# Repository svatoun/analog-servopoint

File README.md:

# analog-servopoint

Analog-servopoint je zařízení určené k ovládání servo a spínaných (zap/vyp) výstupů pro analogově řízený model železnice. Základní deska má tyto vstupy a výstupy:

1. Vstup z maticové klávesnice 4x4 tlačítek. Funguje jak pro spínací mžiková tlačítka, tak pro přepínací tlačítka. U přepínacích tlačítek může mít význam přepnutí do obou poloh.
2. Ovládání až 8 modelářských serv. 
3. 8 tranzistorem spínaných výstupů, zatížení cca 500mA/výstup, celkem 2,5A

Software poskytuje následující funkce:

### Ovládání serva
1. Určení 2 poloh (levá, pravá) pro každé servo.
2. Určení rychlosti přestavování serva.
3. Interaktivní kalibrace serva
4. Plynulé přestavení serva do předdefinované pravé/levé polohy, nebo na libovolný úhel
5. Postupné spínaní serv, eliminaci proudové špičky, omezení zákmitu serva
6. "Ohlas" polohy serva na definovaném spínaném výstupu (ON/OFF)
7. Přestavování 2 serv najednou

### Ovládání jednotlivých výstupů
1. Zapnutí, vypnutí
2. Pulz 300ms, nebo zadané délky
3. (stále ve vývoji) Blikání s určenou dobou zapnutí a prodlevy. Blikání v protifázi.
4. Napájení tranzistorového pole lze volit jumperem, +5V nebo napětí zdroje.

### Reakce na tlačítka
Tlačítka se čtou po sloupcích, v případě přepinačů je nutné zařadit do matice diody.
1. Přiřazení sekvencí pokynů pro serva a spínané výstupy (max 10 akcí)
2. Spuštění sekvence při stisku, rozepnutí tlačítka nebo obojím
3. Vyčkání přestavení serva, nebo provedení několika akcí najednou
4. Při rozepnutí tlačítka je možné celou posloupnost akcí vrátit nebo přerušit
5. Volitelné prodlevy mezi akcemi
6. Postupné vykonání akcí pro tlačítka stisknutá najednou či v těsném sledu (max 20)

### Nastavení, komunikace
1. Deska se nastavuje a může komunikovat pomocí mikroUSB rozhraní Arduina. 
2. Je možné přímo přikazovat jednotlivé akce (spínání, nastavení serva)
3. Jednoduchý textový výpis konfigurace pro zálohování
4. Upgrade obslužného SW - pomocí Arduino IDE

Podrobnosti viz [Wiki](https://github.com/svatoun/analog-servopoint/wiki/)

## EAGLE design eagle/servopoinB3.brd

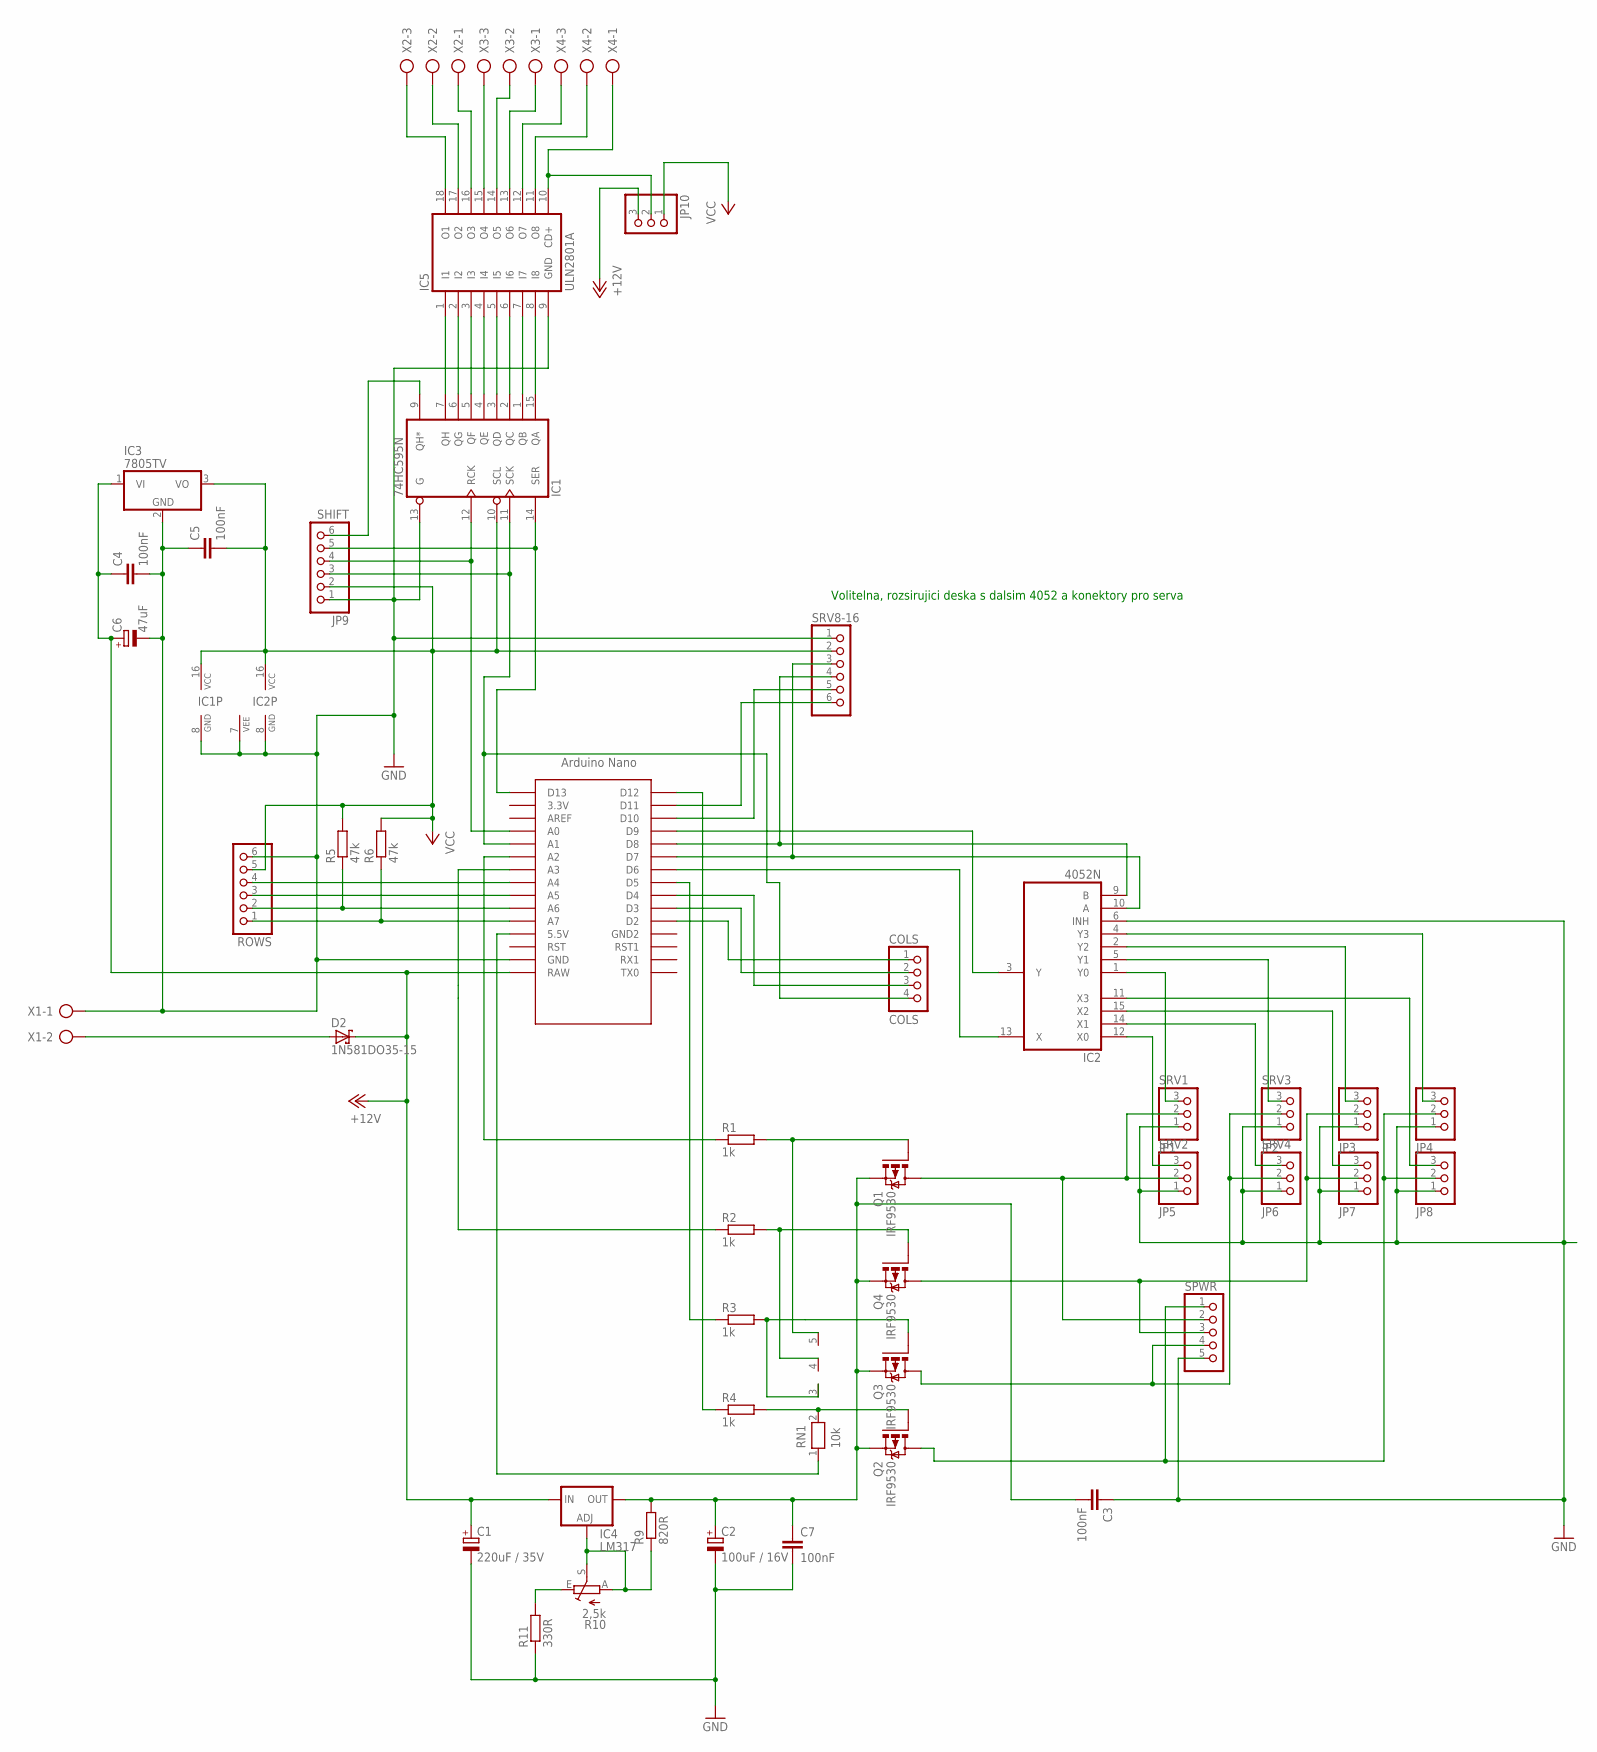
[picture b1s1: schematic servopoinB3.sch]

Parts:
C1: 220uF / 35V; E5-10,5
C2: 100uF / 16V; E2,5-5
C3, C4, C5, C7: 100nF; C025-025X050
C6: 47uF; E2,5-6
COLS: COLS; 1X04
D2: 1N581DO35-15; DO35-10
IC1: 74HC595N; DIL16
IC2: 4052N; DIL16
IC3: 7805TV; TO220V
IC4: LM317; 317TS
IC5: ULN2801A; DIL18
JP1: SRV1; 1X03
JP2: SRV3; 1X03
JP3, JP4, JP7, JP8, JP10: PINHD-1X3; 1X03
JP5: SRV2; 1X03
JP6: SRV4; 1X03
JP9: SHIFT; 1X06
Q1, Q2, Q3, Q4: IRF9530; TO220BV
R1, R2, R3, R4: 1k; 0207/10
R5, R6: 47k; 0207/10
R9: 820R; 0207/10
R10: 2,5k; LI10
R11: 330R; 0207/10
RN1: 10k; RN-5
ROWS: PINHD-1X6; 1X06
SPWR: PINHD-1X5; 1X05
SRV8-16: PINHD-1X6; 1X06
U$1: NANO
X1: AK500/2
X2, X3, X4: AK500/3

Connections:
+12V: C1.+, C4.1, C6.+, D2.C, IC3.1 (VI), IC4.3 (IN), JP10.3, U$1.RAW
GND: C1.-, C2.-, C3.1, C4.2, C5.1, C6.-, C7.2, IC1.8 (GND), IC1.13 (G), IC2.6 (INH), IC2.7 (VEE), IC2.8 (GND), IC3.2 (GND), IC5.9 (GND), JP1.1, JP2.1, JP3.1, JP4.1, JP5.1, JP6.1, JP7.1, JP8.1, JP9.1, R11.1, ROWS.6, SPWR.5, SRV8-16.1, U$1.GND, X1.1
unnamed: IC2.13 (X), U$1.D6
unnamed: IC2.3 (Y), U$1.D9
unnamed: IC1.15 (QA), IC5.8 (I8)
unnamed: COLS.4, IC1.11 (SCK), JP9.3, U$1.A1
unnamed: IC2.12 (X0), JP5.3
unnamed: IC2.1 (Y0), JP1.3
unnamed: IC2.14 (X1), JP6.3
unnamed: IC2.5 (Y1), JP2.3
unnamed: IC2.15 (X2), JP7.3
unnamed: IC2.2 (Y2), JP3.3
unnamed: IC2.11 (X3), JP8.3
unnamed: IC2.4 (Y3), JP4.3
unnamed: Q1.G, R1.2, RN1.5
unnamed: JP2.2, JP6.2, Q3.D, SPWR.4
unnamed: R6.1, ROWS.1, U$1.A7
unnamed: R2.1, U$1.A3
unnamed: Q4.G, R2.2, RN1.4
unnamed: R3.1, U$1.D5
unnamed: Q3.G, R3.2, RN1.3
unnamed: RN1.1, U$1.5V (5.5V)
unnamed: Q2.G, R4.2, RN1.2
unnamed: JP3.2, JP7.2, Q4.D, SPWR.3
unnamed: R4.1, U$1.D12
unnamed: R1.1, U$1.A2
unnamed: D2.A, X1.2
unnamed: ROWS.4, U$1.A4
unnamed: ROWS.3, U$1.A5
unnamed: R5.1, ROWS.2, U$1.A6
unnamed: SRV8-16.6, U$1.D11
unnamed: COLS.2, U$1.D3
unnamed: COLS.3, U$1.D4
unnamed: COLS.1, U$1.D2
unnamed: SRV8-16.5, U$1.D10
unnamed: IC1.14 (SER), JP9.5, U$1.D13
unnamed: IC1.1 (QB), IC5.7 (I7)
unnamed: IC1.9 (QH*), JP9.6
unnamed: IC1.12 (RCK), JP9.4, U$1.A0
unnamed: C2.+, C3.2, C7.1, IC4.2 (OUT), Q1.S, Q2.S, Q3.S, Q4.S, R9.2
unnamed: IC5.10 (CD+), JP10.2, X4.1
unnamed: IC1.2 (QC), IC5.6 (I6)
unnamed: IC1.3 (QD), IC5.5 (I5)
unnamed: IC1.4 (QE), IC5.4 (I4)
unnamed: IC1.5 (QF), IC5.3 (I3)
unnamed: IC1.6 (QG), IC5.2 (I2)
unnamed: IC1.7 (QH), IC5.1 (I1)
unnamed: IC5.18 (O1), X2.3
unnamed: IC4.1 (ADJ), R9.1, R10.A, R10.S
unnamed: R10.E, R11.2
unnamed: IC5.17 (O2), X2.2
unnamed: JP1.2, JP5.2, Q1.D, SPWR.2
unnamed: IC5.16 (O3), X2.1
unnamed: JP4.2, JP8.2, Q2.D, SPWR.1
unnamed: IC5.15 (O4), X3.3
unnamed: IC5.14 (O5), X3.2
unnamed: IC5.13 (O6), X3.1
unnamed: IC5.12 (O7), X4.3
unnamed: IC5.11 (O8), X4.2
unnamed: IC2.9 (B), SRV8-16.4, U$1.D8
unnamed: IC2.10 (A), SRV8-16.3, U$1.D7
VCC: C5.2, IC1.10 (SCL), IC1.16 (VCC), IC2.16 (VCC), IC3.3 (VO), JP9.2, JP10.1, R5.2, R6.2, ROWS.5, SRV8-16.2

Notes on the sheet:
Volitelna, rozsirujici deska s dalsim 4052 a konektory pro serva

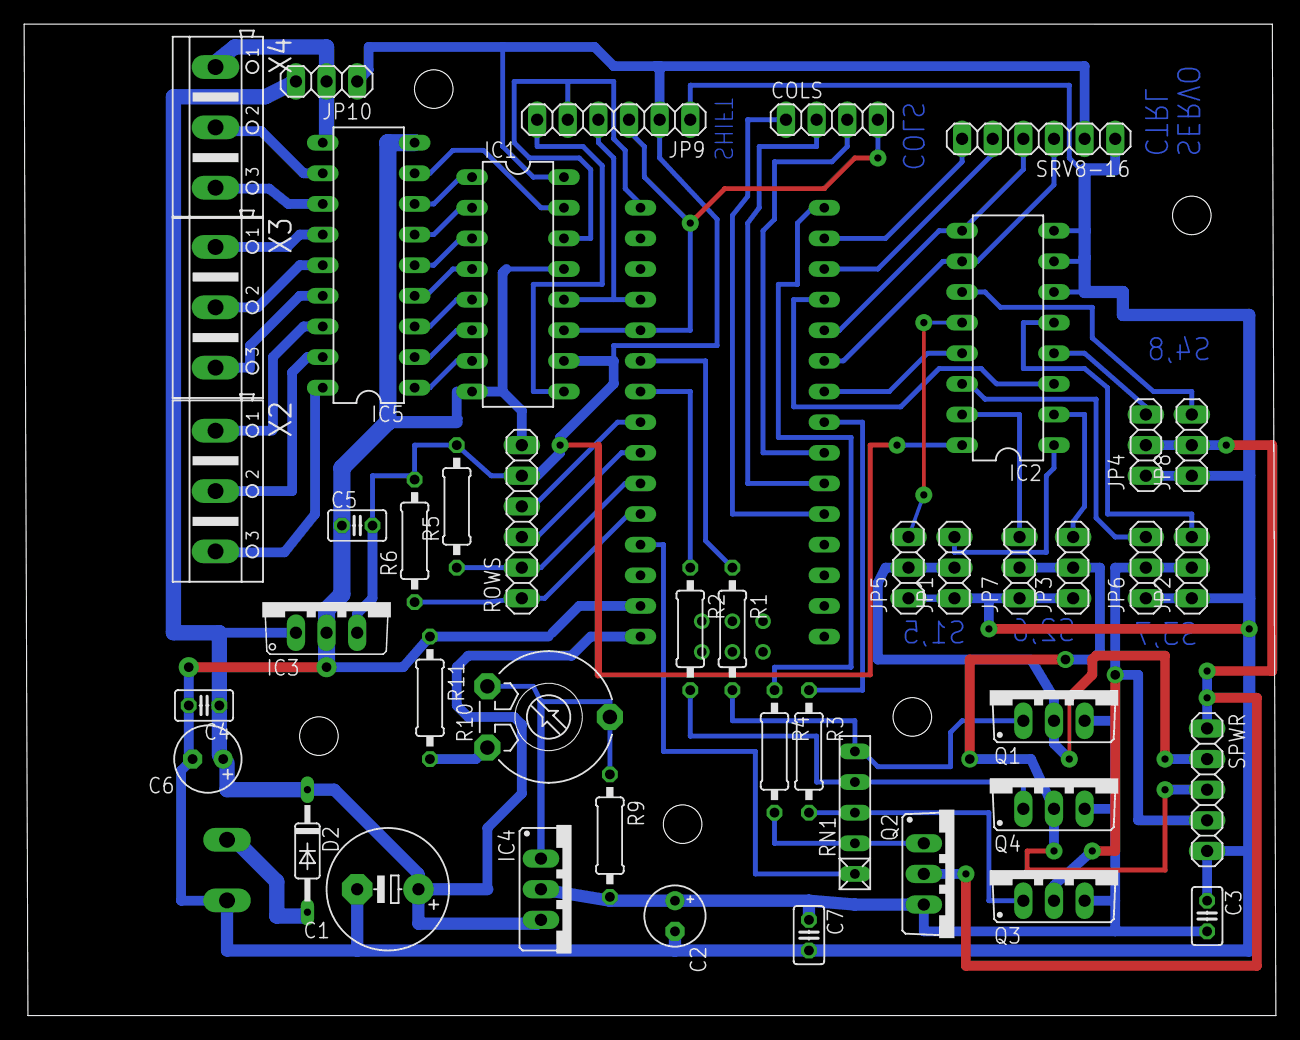
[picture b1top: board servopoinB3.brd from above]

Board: 2 copper layers, 103.8 x 82.2 mm, 46 parts (1 on the bottom side), 62 nets.

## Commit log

2018-03-02 Baseline
2018-03-04 Added forked and optimized Keypad library
2018-03-04 Work in progress
2018-03-04 Disambiguated headers, added warning on original Keypad conflict
2018-03-04 Upgraded to Keypad2 usage
2018-03-04 More descriptive parameter
2018-03-04 Servo configuration stored only in EEPROM, saving 50 byte
2018-03-04 Implemented simple on/off/toggle command
2018-03-04 Minor cleanup
2018-03-05 Rewritten Actions to be stored only in EEPROM. Initialization that depends on globals moved out of constructors to boot() methods run from ModuleChain. Used SoftwareServo (#define)
2018-03-07 Set latch low so that keyboard may use the clock pin
2018-03-07 not DEBUG disables all debug messages
2018-03-07 Unusccessful experiments, put aside
2018-03-10 More command modes, bugfixes in servo
2018-03-10 Implemented servo feedback
2018-03-10 Servo feedback restored after power on
2018-03-11 Prototype, too much memory consumed
2018-03-12 fixed definition of new range - output is reset
2018-03-12 Play command implemented; interactive control
2018-03-14 Eagle files
2018-03-14 Started readme
2018-03-14 More readme
2018-03-21 Fixed readme
2018-03-27 Refactored delayed action cancel, bugfixes
2018-03-30 Pointer optimization
2018-03-30 Avoid erroneous unhandled message
2018-03-30 Array loop optimizations. Do not wave servos when idle
2018-03-30 Bugfixes, wait time printed
2018-03-30 Fixed bugs in scheduler, wait command works
2018-03-31 Lowercased input line
2018-03-31 Shortened strings, removed excess setup
2018-03-31 Optimized furhter, bugfixes for scheduler, implemented flashing
2018-03-31 Small cleanup
2018-03-31 Removed old OO NumberInput
2018-04-01 Refactored input to simple char* not String
2018-04-01 Added "full" retcode from processors, to discard unknown actions. Minor cleanup - obsolete processor API
2018-04-01 Attempt to remove String and realloc
2018-04-01 Removed sprintfs, replaced by itoa and strcat
2018-04-04 Added state tracking for conditions
2018-04-04 Linked Wiki
2018-04-04 Absolute link
2018-04-05 Better prompt
2018-04-05 Converted integer -> char, byte
2018-04-05 Added missing int > byte conversion
2018-04-05 Fixed missing newline
2018-04-07 Moved so that Arduino IDE recognizes the sketch
2018-05-16 Verze B3 se svorkovnici
2018-08-02 Opraveny nespravny play mode
2018-09-16 Uprava pro vstup z RS485, zrusena maticova klavesnice
2018-10-06 Bugfixes
2018-10-29 Pridano rozsiren SBUS
